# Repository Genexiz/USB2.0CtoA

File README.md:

# USB C Receptacle to USB A Plug Adapter
>Work in Progress
**USBC to A Adapter (USB2.0) with 2-layers PCB**

This is my hobby project for practicing circuit design and PCB design skills
<br>
<br>

## Schematic

## PCB

>_AI used in this project -> Gemini 3.7 flash (For suggest method how to design a schematic)_

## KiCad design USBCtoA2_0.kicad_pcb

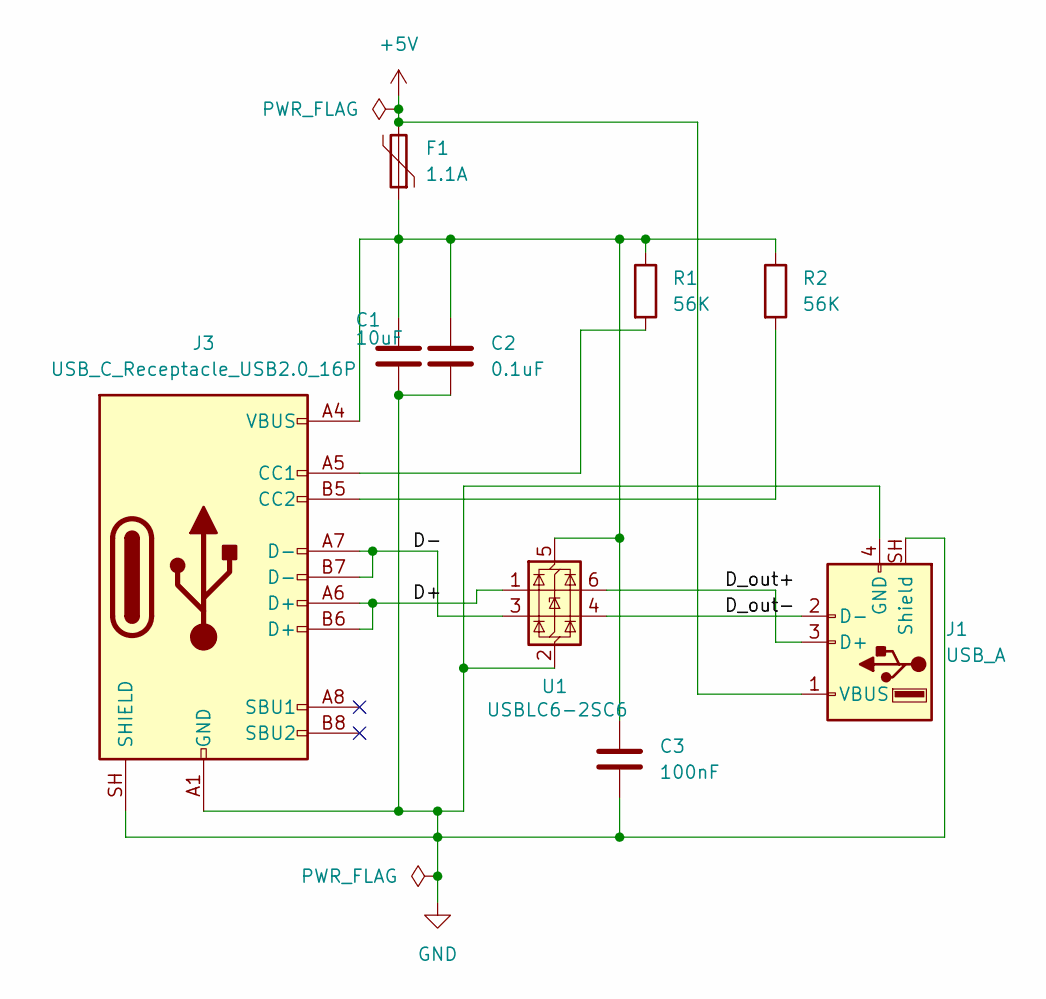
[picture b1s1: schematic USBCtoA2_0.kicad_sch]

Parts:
C1: 10uF; C_1206_3216Metric_Pad1.33x1.80mm_HandSolder
C2: 0.1uF; C_0805_2012Metric_Pad1.18x1.45mm_HandSolder
C3: 100nF; C_0805_2012Metric_Pad1.18x1.45mm_HandSolder
F1: 1.1A; Fuse_1812_4532Metric_Pad1.30x3.40mm_HandSolder
J1: USB_A; USB_A_Molex_48037-2200_Horizontal
J3: USB_C_Receptacle_USB2.0_16P; USB_C_Receptacle_G-Switch_GT-USB-7010ASV
R1, R2: 56K; R_1206_3216Metric_Pad1.30x1.75mm_HandSolder
U1: USBLC6-2SC6; SOT-23-6

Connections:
+5V: F1.2, J1.1 (VBUS)
/D+: J3.A6 (D+), J3.B6 (D+), U1.1 (I/O1)
/D-: J3.A7 (D-), J3.B7 (D-), U1.3 (I/O2)
/D_out+: J1.3 (D+), U1.6 (I/O1)
/D_out-: J1.2 (D-), U1.4 (I/O2)
GND: C1.2, C2.2, C3.2, J1.4 (GND), J1.SH (Shield), J3.A1 (GND), J3.A12 (GND), J3.B1 (GND), J3.B12 (GND), J3.SH (SHIELD), U1.2 (GND)
unnamed: J3.A5 (CC1), R1.2
unnamed: J3.B5 (CC2), R2.2
unnamed: C1.1, C2.1, C3.1, F1.1, J3.A4 (VBUS), J3.A9 (VBUS), J3.B4 (VBUS), J3.B9 (VBUS), R1.1, R2.1, U1.5 (VBUS)

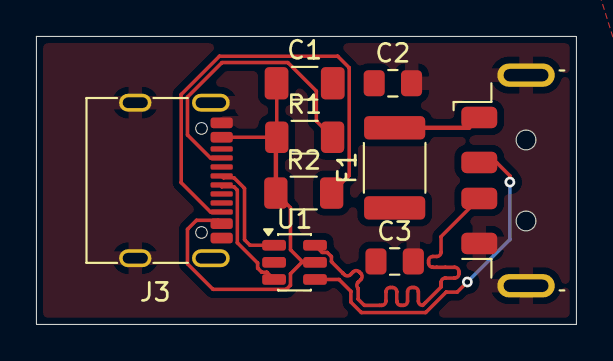
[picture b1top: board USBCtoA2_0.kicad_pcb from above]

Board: 2 copper layers, 30.0 x 16.0 mm, 9 parts (0 on the bottom side), 9 nets.
